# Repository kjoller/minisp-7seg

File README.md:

MiniSP-7seg
====================

A small (5x2½cm) MSP430G2xxx-board with a 4 digit 7 segment display.

Port 2 (and P1.0) is used for the seven digit display through a 
74HC595 shift register, leaving P1.1-P1.7 for other uses. The anode of the 
display digits are connected via transistors to PWM pins, allowing the
brightness to be adjusted

There is a 4 pin SBW programming header on the one side, and a breakout
for the serial out from the shift register - useful for adding another,
external shift register

R1-R8 is noted as 150R in the schematic, but can be anywhere from 100R to 1K.
Brightness can be adjusted this way.

The colon on the seven segment display can be activated (taking up P1.3) by 
adding R14 and R15.

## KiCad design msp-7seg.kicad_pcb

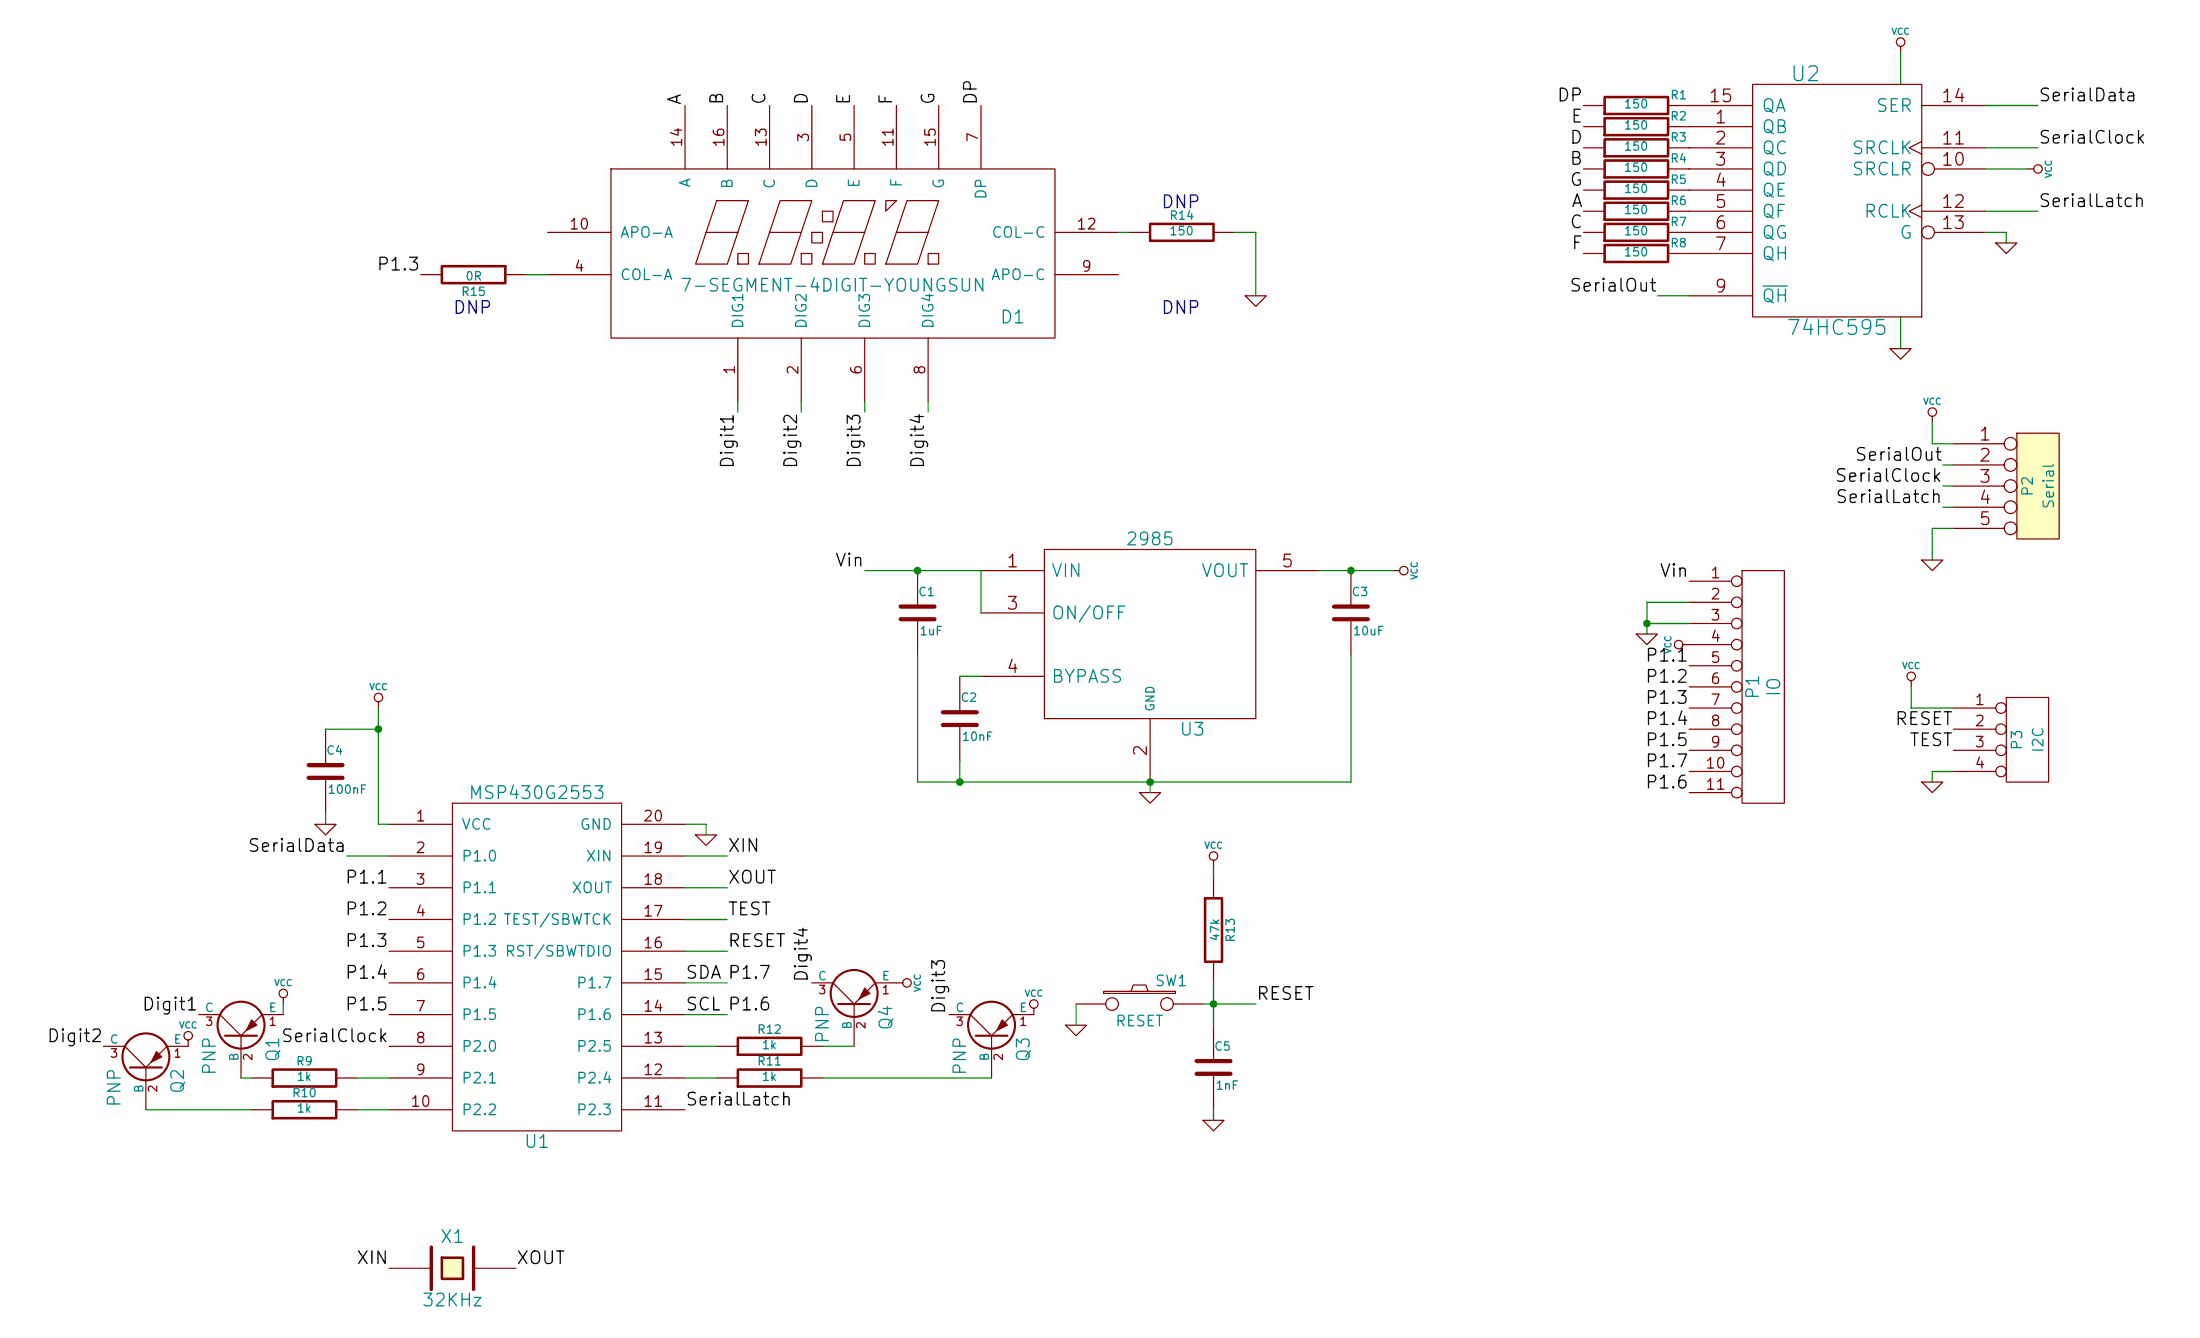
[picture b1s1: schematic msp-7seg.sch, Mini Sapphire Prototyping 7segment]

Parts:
C1: 1uF
C2: 10nF
C3: 10uF
C4: 100nF
C5: 1nF
D1: 7-SEGMENT-4DIGIT-YOUNGSUN
P1: IO
P2: Serial
P3: I2C
Q1, Q2, Q3, Q4: PNP
R1, R2, R3, R4, R5, R6, R7, R8, R14: 150
R9, R10, R11, R12: 1k
R13: 47k
R15: 0R
SW1: RESET
U1: MSP430G2553
U2: 74HC595
U3: 2985
X1: 32KHz

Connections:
/A: D1.14 (A), R6.1
/B: D1.16 (B), R4.1
/C: D1.13 (C), R7.1
/D: D1.3 (D), R3.1
/DP: D1.7 (DP), R1.1
/Digit1: D1.1 (DIG1), Q1.3 (C)
/Digit2: D1.2 (DIG2), Q2.3 (C)
/Digit3: D1.6 (DIG3), Q3.3 (C)
/Digit4: D1.8 (DIG4), Q4.3 (C)
/E: D1.5 (E), R2.1
/F: D1.11 (F), R8.1
/G: D1.15 (G), R5.1
/P1.1: P1.5, U1.3 (P1.1)
/P1.2: P1.6, U1.4 (P1.2)
/P1.3: P1.7, R15.2, U1.5 (P1.3)
/P1.4: P1.8, U1.6 (P1.4)
/P1.5: P1.9, U1.7 (P1.5)
/P1.6: P1.11, U1.14 (P1.6)
/P1.7: P1.10, U1.15 (P1.7)
/RESET: C5.1, P3.2, R13.2, SW1.2, U1.16 (RST/SBWTDIO)
/SerialClock: P2.3, U1.8 (P2.0), U2.11 (SRCLK)
/SerialData: U1.2 (P1.0), U2.14 (SER)
/SerialLatch: P2.4, U1.11 (P2.3), U2.12 (RCLK)
/SerialOut: P2.2, U2.9 (~QH)
/TEST: P3.3, U1.17 (TEST/SBWTCK)
/Vin: C1.1, P1.1, U3.1 (VIN), U3.3 (ON/OFF)
/XIN: U1.19 (XIN), X1.1
/XOUT: U1.18 (XOUT), X1.2
GND: C1.2, C2.2, C3.2, C4.2, C5.2, P1.2, P1.3, P2.5, P3.4, R14.2, SW1.1, U1.20 (GND), U2.8 (GND), U2.13 (G), U3.2 (GND)
unnamed: C2.1, U3.4 (BYPASS)
unnamed: D1.4 (COL-A), R15.1
unnamed: D1.12 (COL-C), R14.1
unnamed: Q1.2 (B), R9.1
unnamed: Q2.2 (B), R10.1
unnamed: Q3.2 (B), R11.2
unnamed: Q4.2 (B), R12.2
unnamed: R1.2, U2.15 (QA)
unnamed: R2.2, U2.1 (QB)
unnamed: R3.2, U2.2 (QC)
unnamed: R4.2, U2.3 (QD)
unnamed: R5.2, U2.4 (QE)
unnamed: R6.2, U2.5 (QF)
unnamed: R7.2, U2.6 (QG)
unnamed: R8.2, U2.7 (QH)
unnamed: R9.2, U1.9 (P2.1)
unnamed: R10.2, U1.10 (P2.2)
unnamed: R11.1, U1.12 (P2.4)
unnamed: R12.1, U1.13 (P2.5)
VCC: C3.1, C4.1, P1.4, P2.1, P3.1, Q1.1 (E), Q2.1 (E), Q3.1 (E), Q4.1 (E), R13.1, U1.1 (VCC), U2.10 (SRCLR), U2.16 (VCC), U3.5 (VOUT)

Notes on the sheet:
DNP

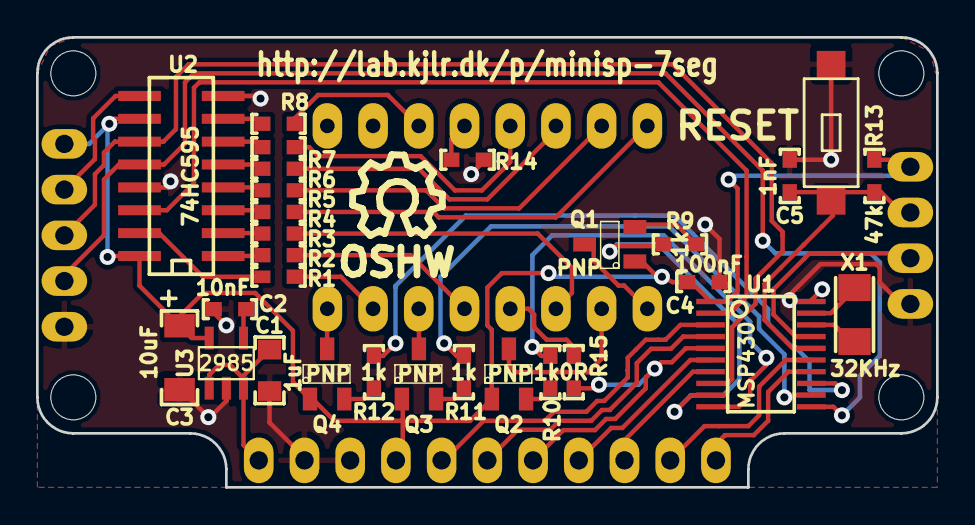
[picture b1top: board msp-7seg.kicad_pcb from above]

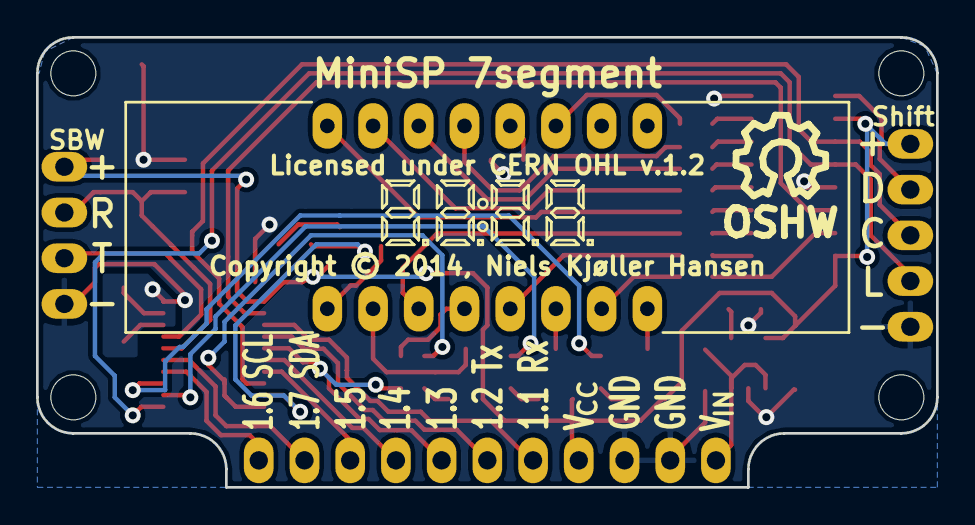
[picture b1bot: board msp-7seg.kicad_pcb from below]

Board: 2 copper layers, 50.0 x 25.0 mm, 39 parts (8 on the bottom side), 49 nets.

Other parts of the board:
MH: MountingHole_2-7mm_RevA_Date21Jun2010; MountingHole_2-5mm
MH#2, MH#3, MH#4: MountingHole_2-7mm_RevA_Date21Jun2010; MountingHole_2-5mm
SYM: Symbol_OSHW-Logo_SilkScreen_07Jul2012; Symbol_OSHW-Logo_SilkScreen
SYM#2: Symbol_OSHW-Logo_SilkScreen_07Jul2012; Symbol_OSHW-Logo_SilkScreen

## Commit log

2014-02-26 Initial commit - just missing a reset button
2014-02-26 Spread out components and added reset button
2014-02-27 Cleaned up silkscreen, added gerbers, schematic and images
2014-03-01 Added breakout for shift register
2014-03-03 Made a 5x5cm mini panel and added to the README.

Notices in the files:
msp-7seg.kicad_pcb:
Licensed under CERN OHL v.1.2
Copyright © 2014, Niels Kjøller Hansen
